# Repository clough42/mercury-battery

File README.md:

# mercury-battery
Replacement for vintage mercury batteries used in gage amplifiers and other instruments

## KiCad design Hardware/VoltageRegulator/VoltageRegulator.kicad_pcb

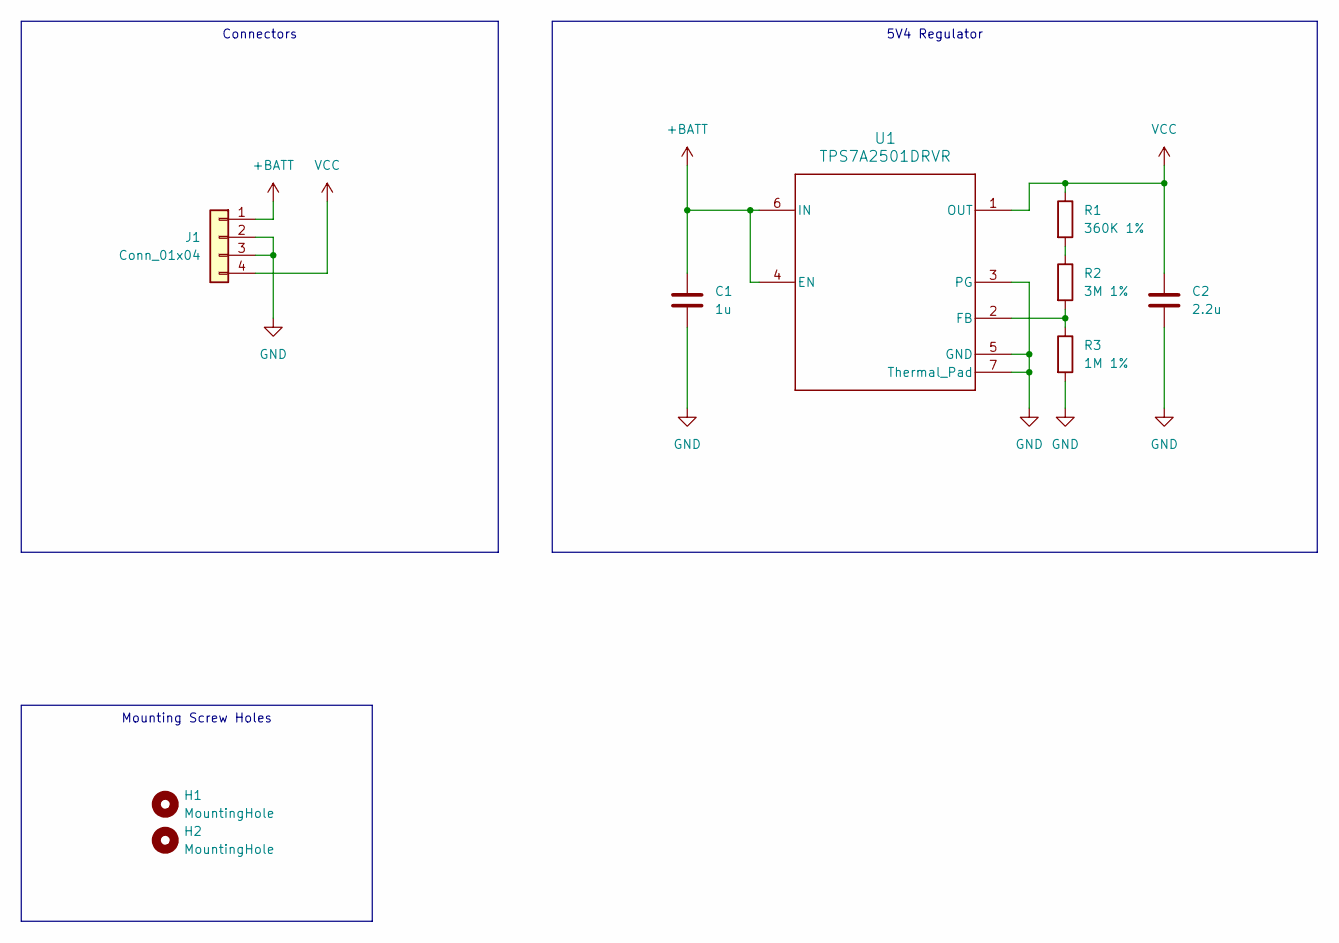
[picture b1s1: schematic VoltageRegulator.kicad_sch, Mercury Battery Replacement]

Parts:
C1: 1u; C_0805_2012Metric; LCSC Part # C28323
C2: 2.2u; C_0805_2012Metric; LCSC Part # C49217
H1, H2: MountingHole; MountingHole_3.5mm
J1: Conn_01x04; PinHeader_1x04_P2.54mm_Vertical
R1: 360K 1%; R_0603_1608Metric; LCSC Part # C352328
R2: 3M 1%; R_0603_1608Metric; LCSC Part # C269653
R3: 1M 1%; R_0603_1608Metric; LCSC Part # C3016422
U1: TPS7A2501DRVR; DRV0006A-IPC_C; LCSC Part # C2864326

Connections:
+BATT: C1.1, J1.1, U1.4 (EN), U1.6 (IN)
GND: C1.2, C2.2, J1.2, J1.3, R3.2, U1.3 (PG), U1.5 (GND), U1.7 (Thermal_Pad)
unnamed: R1.2, R2.1
unnamed: R2.2, R3.1, U1.2 (FB)
VCC: C2.1, J1.4, R1.1, U1.1 (OUT)

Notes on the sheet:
5V4 Regulator
Mounting Screw Holes
Connectors

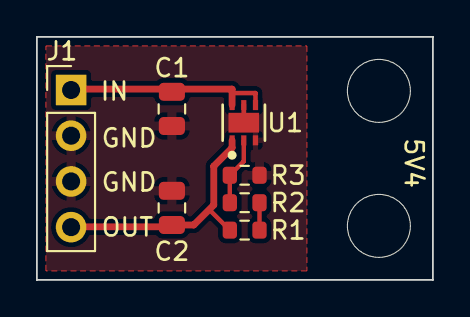
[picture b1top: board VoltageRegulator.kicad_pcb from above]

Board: 2 copper layers, 22.0 x 13.5 mm, 9 parts (0 on the bottom side), 5 nets.

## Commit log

2023-06-07 First schematic and PCB layout
2023-06-07 Layout changes plus 3D model
2023-06-08 Smaller board with isolated mounting holes
2023-06-08 Generate Gerber and drill files.
2023-06-08 Move 3D model to hardware directory
2023-06-08 Clean up production files
2023-06-08 Exclude through-hole header from BOM
2023-06-09 Neaten up schematic, add precision designators for resistors
2023-06-10 Mmmmm...metric
2023-06-12 Exclude irrelevant rule checks.
2023-06-12 DRC Exclusions
2023-06-12 Add LCSC part numbers
2023-06-12 Don't populate header pints
2023-06-29 Add test probe carrier PCB
2023-07-01 Update STEP file
2023-07-01 Moved test probe carrier folder
2023-07-05 Update license - add name
2023-07-13 Add STEP file
